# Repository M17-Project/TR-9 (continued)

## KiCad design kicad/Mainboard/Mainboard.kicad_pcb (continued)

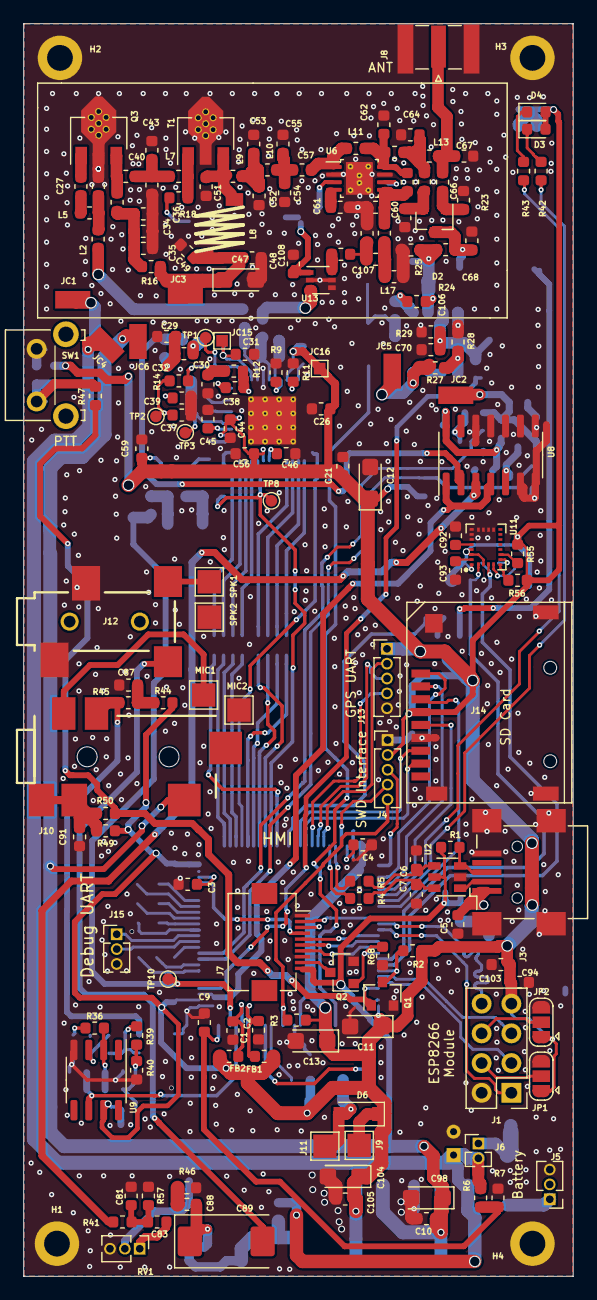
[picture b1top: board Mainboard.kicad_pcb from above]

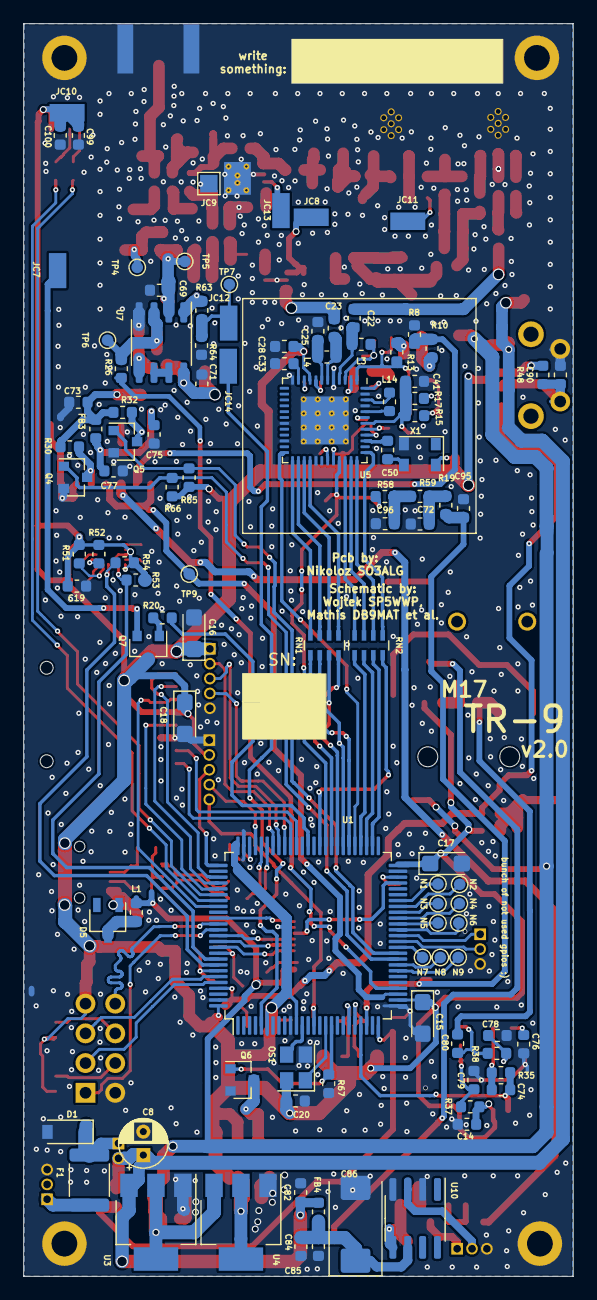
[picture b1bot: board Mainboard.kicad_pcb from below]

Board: 2 copper layers, 47.0 x 107.1 mm, 279 parts (105 on the bottom side), 177 nets.

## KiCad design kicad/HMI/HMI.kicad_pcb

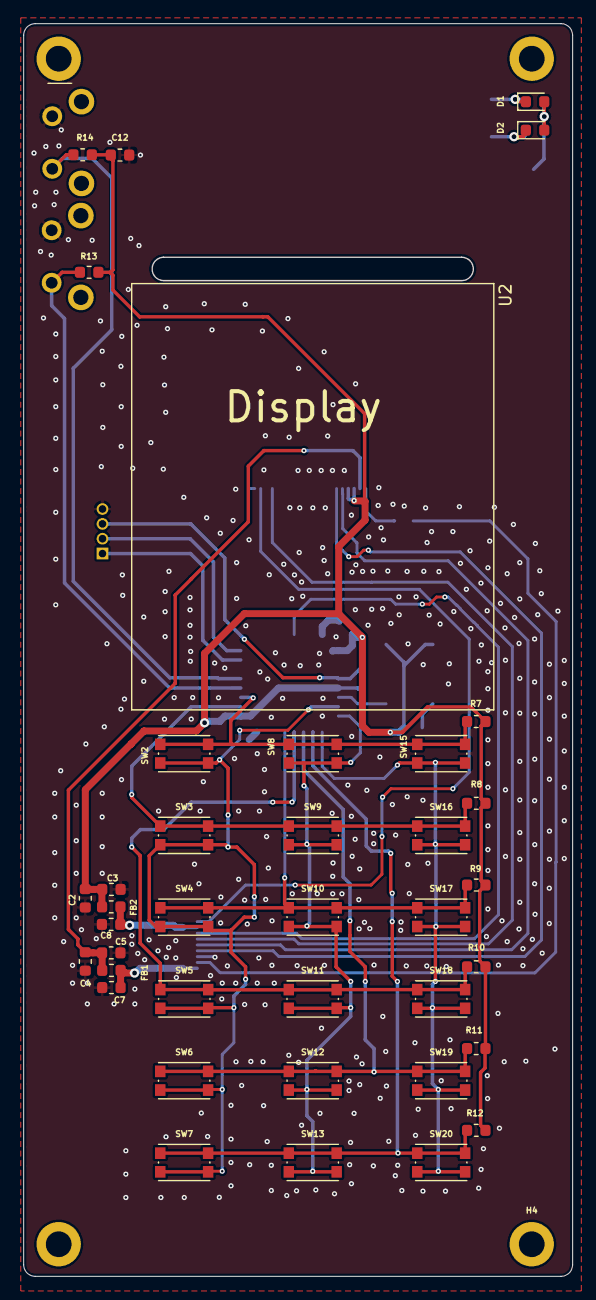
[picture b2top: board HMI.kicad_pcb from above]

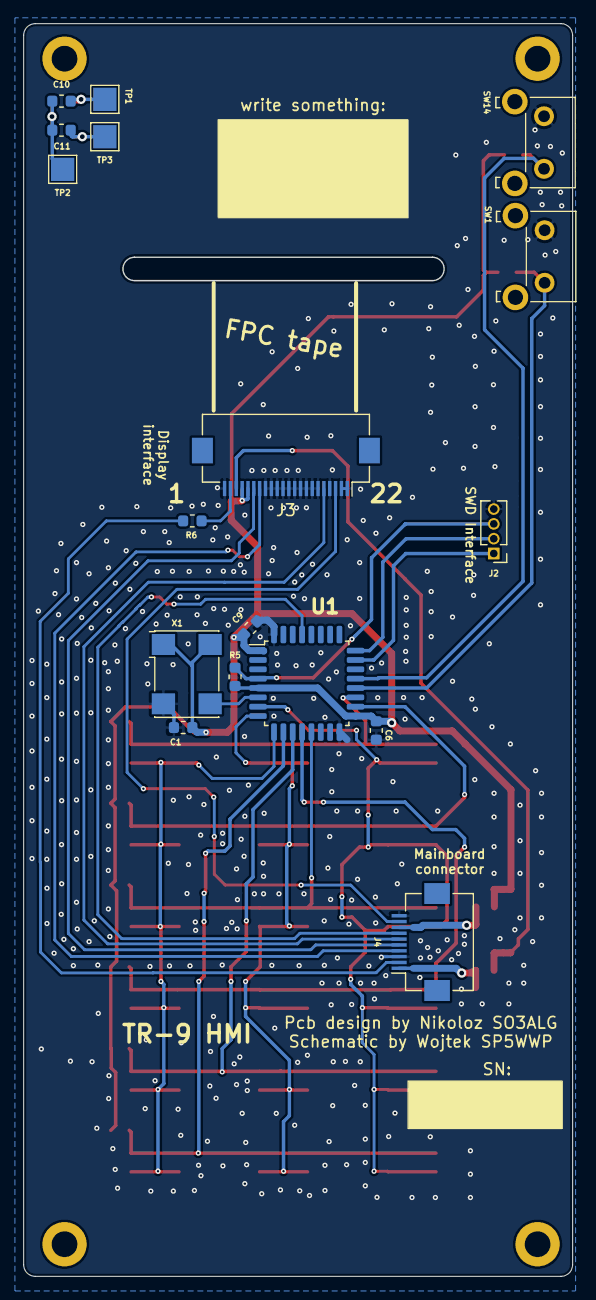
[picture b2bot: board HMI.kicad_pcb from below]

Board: 2 copper layers, 47.0 x 107.2 mm, 59 parts (17 on the bottom side), 30 nets.

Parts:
C1: 10n; C_0603_1608Metric
C2, C4, C7, C8, C10, C11: 100n; C_0603_1608Metric
C3, C5, C6, C9, C12: 1u; C_0603_1608Metric
D1, D2: LED; D_0603_1608Metric
FB1, FB2: Ferrite_Bead; L_0603_1608Metric
H1, H2, H3, H4: M2; MountingHole_2.2mm_M2_ISO14580_Pad
J2: SWD; PinHeader_1x04_P1.27mm_Vertical
J3: FH12-22S-0.5SH; Hirose_FH12-22S-0.5SH_1x22-1MP_P0.50mm_Horizontal
J4: RIBBON; Hirose_FH12-10S-0.5SH_1x10-1MP_P0.50mm_Horizontal
R5: 10k; R_0603_1608Metric
R6: 47R; R_0603_1608Metric
R7, R8, R9, R10, R11, R12, R13, R14: 47k; R_0603_1608Metric
SW1, SW14: SW_Push; SW_Tactile_SKHH_Angled
SW2, SW3, SW4, SW5, SW6, SW7, SW8, SW9, SW10, SW11, SW12, SW13, SW15, SW16, SW17, SW18, SW19, SW20: SW_Push; SW_Push_1P1T_NO_CK_KMR2
TP1, TP2, TP3: TestPoint; TestPoint_Pad_2.0x2.0mm
U1: STM32L011K4Tx; LQFP-32_7x7mm_P0.8mm
U2: DEM 128128A TMH-PW-N; DEM_128128A_TMH-PW-N
X1: ASV-4.000MHZ-EJ-T; Oscillator_SMD_Abracon_ASV-4Pin_7.0x5.1mm

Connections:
+3V3: C1.1, C2.1, C3.1, C6.1, C9.1, C12.1, FB2.2, J3.18, J3.19, R5.1, R7.1, R8.1, R9.1, R10.1, R11.1, R12.1, R13.1, R14.1, U1.1, U1.5, U1.17, X1.1, X1.4
+5V: C4.1, C5.1, FB1.2, J3.20
C1: SW2.2, SW3.2, SW4.2, SW5.2, SW6.2, SW7.2, U1.7
C2: SW8.2, SW9.2, SW10.2, SW11.2, SW12.2, SW13.2, U1.8
C3: SW15.2, SW16.2, SW17.2, SW18.2, SW19.2, SW20.2, U1.9
F1: R13.2, SW1.2, U1.20
F2: R14.2, SW14.2, U1.21
GND: C1.2, C2.2, C3.2, C4.2, C5.2, C6.2, C7.2, C8.2, C9.2, C12.2, J2.4, J3.1, J3.2, J3.4, J3.6, J3.7, J3.8, J3.9, J3.10, J3.11, J3.12, J3.13, J3.14, J3.15, J3.22, J4.3, J4.10, SW1.1, SW14.1, U1.16, U1.32, X1.2
NRST: J2.3, R5.2, U1.4
unnamed: C7.1, FB1.1, J4.1
unnamed: C8.1, FB2.1, J4.8
unnamed: C10.1, C11.1, D1.2, D2.2, TP2.1
unnamed: C10.2, D1.1, TP1.1
unnamed: C11.2, D2.1, TP3.1
unnamed: J3.21, R6.2
OSC: U1.6, X1.3
R1: R12.2, SW7.1, SW13.1, SW20.1, U1.10
R2: R11.2, SW6.1, SW12.1, SW19.1, U1.11
R3: R10.2, SW5.1, SW11.1, SW18.1, U1.12
R4: R9.2, SW4.1, SW10.1, SW17.1, U1.13
R5: R8.2, SW3.1, SW9.1, SW16.1, U1.18
R6: R7.2, SW2.1, SW8.1, SW15.1, U1.19
SPI1_CS: J3.16, J4.4
SPI1_MOSI: J3.5, J4.6
SPI1_SCK: J3.17, J4.5
SWCLK: J2.2, U1.24
SWDIO: J2.1, U1.23
TFT_LED: J4.2, R6.1
TFT_RST: J3.3, J4.9
TX: J4.7, U1.29

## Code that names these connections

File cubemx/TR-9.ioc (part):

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Mcu.Name=STM32F777VITx
Mcu.Package=LQFP100
Mcu.UserName=STM32F777VITx
PA0/WKUP.Signal=ADCx_IN0
PA1.Signal=ADCx_IN1
PA10.Mode=Asynchronous
PA10.Signal=USART1_RX
PA11.Mode=Device_Only
PA11.Signal=USB_OTG_FS_DM
PA12.Mode=Device_Only
PA12.Signal=USB_OTG_FS_DP
PA13.Mode=Serial_Wire
PA13.Signal=SYS_JTMS-SWDIO
PA14.Mode=Serial_Wire
PA14.Signal=SYS_JTCK-SWCLK
PA3.Signal=ADCx_IN3
PA4.Signal=COMP_DAC1_group
PA5.Signal=COMP_DAC2_group
PA8.GPIOParameters=GPIO_Label
PA8.GPIO_Label=GPS_EN
PA8.Signal=GPIO_Output
PA9.Mode=Asynchronous
PA9.Signal=USART1_TX
PB0.GPIOParameters=PinState,GPIO_Label
PB0.GPIO_Label=SPK_AMP_SEL
PB0.PinState=GPIO_PIN_SET
PB0.Signal=GPIO_Output
PB1.GPIOParameters=PinState,GPIO_Label
PB1.GPIO_Label=FM_MOD_SEL
PB1.PinState=GPIO_PIN_SET
PB1.Signal=GPIO_Output
PB10.Mode=Asynchronous
PB10.Signal=USART3_TX
PB11.Mode=Asynchronous
PB11.Signal=USART3_RX
PB13.Mode=Full_Duplex_Master
PB13.Signal=SPI2_SCK
PB14.GPIOParameters=GPIO_PuPd
PB14.GPIO_PuPd=GPIO_PULLUP
PB14.Mode=Full_Duplex_Master
PB14.Signal=SPI2_MISO
PB15.GPIOParameters=GPIO_PuPd
PB15.GPIO_PuPd=GPIO_PULLUP
PB15.Mode=Full_Duplex_Master
PB15.Signal=SPI2_MOSI
PB2.GPIOParameters=GPIO_Label
PB2.GPIO_Label=N7
PB2.Signal=GPIO_Output
PB3.Mode=Simplex_Bidirectional_Master
PB3.Signal=SPI1_SCK
PB4.GPIOParameters=GPIO_Speed,PinState,GPIO_Label
PB4.GPIO_Label=SPI1_CS
PB4.GPIO_Speed=GPIO_SPEED_FREQ_VERY_HIGH
PB4.PinState=GPIO_PIN_SET
PB4.Signal=GPIO_Output
PB5.GPIOParameters=GPIO_Label
PB5.GPIO_Label=BLIGHT_CTRL
PB5.Signal=S_TIM3_CH2
PB6.Mode=I2C
PB6.Signal=I2C1_SCL
PB7.Mode=I2C
PB7.Signal=I2C1_SDA
PB8.GPIOParameters=PinState,GPIO_Label
PB8.GPIO_Label=WIFI_RST
PB8.PinState=GPIO_PIN_SET
PB8.Signal=GPIO_Output
PB9.GPIOParameters=GPIO_Label
PB9.GPIO_Label=WIFI_EN
PB9.Signal=GPIO_Output
PC1.GPIOParameters=PinState,GPIO_Label
PC1.GPIO_Label=XO_EN
PC1.PinState=GPIO_PIN_SET
PC1.Signal=GPIO_Output
PC12.GPIOParameters=GPIO_PuPd
PC12.GPIO_PuPd=GPIO_PULLDOWN
PC12.Mode=SD_1_bit
PC12.Signal=SDMMC1_CK
PC2.GPIOParameters=GPIO_Label
PC2.GPIO_Label=VIBRATE
PC2.Signal=GPIO_Output
PC4.GPIOParameters=GPIO_Label
PC4.GPIO_Label=N9
PC4.Signal=GPIO_Output
PC5.GPIOParameters=GPIO_Label
PC5.GPIO_Label=N8
PC5.Signal=GPIO_Output
PC6.GPIOParameters=GPIO_Speed,PinState,GPIO_Label
PC6.GPIO_Label=LNA_EN
PC6.GPIO_Speed=GPIO_SPEED_FREQ_HIGH
PC6.PinState=GPIO_PIN_SET
PC6.Signal=GPIO_Output
PC8.GPIOParameters=GPIO_PuPd
PC8.GPIO_PuPd=GPIO_PULLUP
PC8.Mode=SD_1_bit
PC8.Signal=SDMMC1_D0
PD0.GPIOParameters=PinState,GPIO_Label
PD0.GPIO_Label=LED_GRN
PD0.PinState=GPIO_PIN_SET
PD0.Signal=GPIO_Output
PD1.GPIOParameters=PinState,GPIO_Label
PD1.GPIO_Label=LED_RED
PD1.PinState=GPIO_PIN_SET
PD1.Signal=GPIO_Output
PD10.GPIOParameters=GPIO_Speed,GPIO_Label
PD10.GPIO_Label=ADF_SDATA
PD10.GPIO_Speed=GPIO_SPEED_FREQ_VERY_HIGH
PD10.Signal=GPIO_Output
PD11.GPIOParameters=GPIO_Label
PD11.GPIO_Label=ADF_SREAD
PD11.Signal=GPIO_Input
PD12.GPIOParameters=GPIO_Speed,GPIO_Label
PD12.GPIO_Label=ADF_SCLK
PD12.GPIO_Speed=GPIO_SPEED_FREQ_VERY_HIGH
PD12.Signal=GPIO_Output
PD13.GPIOParameters=GPIO_Label
PD13.GPIO_Label=ADF_SWD
PD13.Signal=GPXTI13
PD14.GPIOParameters=GPIO_Label
PD14.GPIO_Label=ADF_MUX_OUT
PD14.Signal=GPXTI14
PD2.GPIOParameters=GPIO_PuPd
PD2.GPIO_PuPd=GPIO_PULLUP
PD2.Mode=SD_1_bit
PD2.Signal=SDMMC1_CMD
PD4.GPIOParameters=GPIO_Label
PD4.GPIO_Label=TFT_RST
PD4.Signal=GPIO_Output
PD5.Mode=Asynchronous
PD5.Signal=USART2_TX
PD6.Mode=Asynchronous
PD6.Signal=USART2_RX
PD7.Mode=Simplex_Bidirectional_Master
PD7.Signal=SPI1_MOSI
PD8.GPIOParameters=GPIO_Speed,PinState,GPIO_Label
PD8.GPIO_Label=ADF_CE
PD8.GPIO_Speed=GPIO_SPEED_FREQ_VERY_HIGH
PD8.PinState=GPIO_PIN_SET
PD8.Signal=GPIO_Output
PD9.GPIOParameters=GPIO_Speed,GPIO_Label
PD9.GPIO_Label=ADF_SLE
PD9.GPIO_Speed=GPIO_SPEED_FREQ_VERY_HIGH
PD9.Signal=GPIO_Output
PE0.GPIOParameters=GPIO_PuPd,GPIO_Label,GPIO_ModeDefaultEXTI
PE0.GPIO_Label=PTT_INT
PE0.GPIO_ModeDefaultEXTI=GPIO_MODE_IT_RISING_FALLING
PE0.GPIO_PuPd=GPIO_PULLUP
PE0.Signal=GPXTI0
PE10.GPIOParameters=GPIO_Label
PE10.GPIO_Label=N5
PE10.Signal=GPIO_Output
PE11.GPIOParameters=GPIO_Label
PE11.GPIO_Label=N4
PE11.Signal=GPIO_Output
PE12.GPIOParameters=GPIO_Label
PE12.GPIO_Label=N3
PE12.Signal=GPIO_Output
PE13.GPIOParameters=GPIO_Label
PE13.GPIO_Label=N2
PE13.Signal=GPIO_Output
PE14.GPIOParameters=GPIO_Label
PE14.GPIO_Label=N1
PE14.Signal=GPIO_Output
PE6.GPIOParameters=GPIO_Label
PE6.GPIO_Label=TRX_SW
PE6.Signal=GPIO_Output
PE7.Mode=Asynchronous
PE7.Signal=UART7_RX
PE8.Mode=Asynchronous
PE8.Signal=UART7_TX
PE9.GPIOParameters=GPIO_Label
PE9.GPIO_Label=N6
PE9.Signal=GPIO_Output
PH0/OSC_IN.Mode=HSE-External-Clock-Source
PH0/OSC_IN.Signal=RCC_OSC_IN
PH1/OSC_OUT.Mode=HSE-External-Clock-Source
PH1/OSC_OUT.Signal=RCC_OSC_OUT
RCC.HSE_VALUE=16000000
RCC.SYSCLKFreq_VALUE=216000000
RCC.SYSCLKSource=RCC_SYSCLKSOURCE_PLLCLK
board=custom

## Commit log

2019-01-18 sch+pcb
2019-01-18 cubemx+sw4stm32
2019-01-27 Add files via upload
    I have probably finally fixed interrupt priorities :) also - PTT action is now interrupt driven
2019-03-17 Add files via upload
    +ADXL345
2019-05-28 Add files via upload
    WDS3 config file
2019-12-11 Update README.md
    Added PoC info.
2019-12-26 Initial WIP KiCAD schematics
    Initial commit of the schematics redrawn in KiCAD with some fixes applied. Still needs to be cleaned up
2019-12-26 Removed Eagle files
    Transitioning from Eagle to KiCAD
2019-12-27 Added power detector
    Added two missing inductors in the RF output switch and started work on the power detection circuit
2019-12-30 Updated WIP schematics
2020-01-14 Add files via upload
    * replaced Q7 with BSS138
    * new HMI connector (for keypad and display)
2020-01-18 Added ADF7021
2020-01-18 Added BGA6589 gain stage
2020-01-22 Add files via upload
    replaced TCXO with ECS-TXO-3225-122.8-TR
2020-01-22 Add files via upload
    added 2 buttons: F1 and F2
2020-01-27 Add files via upload
    added a resistor to form a voltage divider network (at pin 3 of LM2904) and changed the cap from 100n to 10n
2020-01-28 Annotated parts
2020-01-28 Revert "Annotated parts"
    This reverts commit b309e3bfe0d7a41f96c10818008ed221b92f9604.
2020-01-28 Annotated parts, again.
2020-01-31 Started assigning footprints
2020-02-01 Add files via upload
    ADF7021 pin 36: SPI1_SCK -> SPI2_SCK
2020-02-01 Add files via upload
    C94 -> 10uF
2020-02-04 Add files via upload
    added a Sallen-Key 6kHz anti-aliasing lowpass filter between the ADF (SWD pin) and STM32 (ADC input)
2020-02-08 Add files via upload
    assigned some more footprints
2020-02-09 Add files via upload
    fixed U7 name (LM2904A)
2020-02-13 - Added footprint library - TR-9 - Imported a few footprints - Designed a MicroSD card slot footprint - Assignment footprints to corresponding elements on schematic
2020-02-13 added more footprints
2020-02-13 Assigned SMA as antenna connector
2020-02-13 - designed and added footprint for L8 RF inductor
2020-02-13 Added HMC RF switch Corrected SOIC footprints assignment
2020-02-14 Added thermal vias to BGA6589 footprint Corrected USART to UART
2020-02-14 Added thermal pads to AFT05MS004NT1 RF transistor footprint
2020-02-14 started working on PCB - power supply completed plotted new PDF schematic
2020-02-14 added a capacitor for GPS voltage line footprints - expanded RF transistors ground plane generated new PDF added authors
2020-02-15 Add files via upload
    i've set some footprints and changed that 10-pin connector pin order
2020-02-15 adf7021 and companion passives are quite sorted now
2020-02-15 PCB - connected microSD card to STM32 & USB frontend path routed added a schottky diode PMEG4005ET.215 footprint changed connector J7 pinout - TFT_RST swapped with UART2_RX! schootky diode added to i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
2020-02-15 Corrected outline in PCB
2020-02-15 another pin swap
2020-02-16 PCB updated - added MIC_AMP & SPK_AMP
2020-02-16 added pcb author
2020-02-16 Working on PCB
2020-02-16 PCB update
2020-02-16 Module with OPA340UA U9 made smaller - more space for other modules
2020-02-16 Power supply part occupies less space on pcb!
2020-02-17 added ESP8266EX
2020-02-17 4066 based switch module connected
2020-02-17 PCB improvement, new PDF plot
2020-02-17 optimised an RF section elements placement
2020-02-18 rf part almost done
2020-02-18 PCB improvement - added module with U13
2020-02-18 Critical J7 header pinout change! New schematic PCB plot
2020-02-18 added 5V line to the HMI ribbon
2020-02-19 added voltage divider at the PA_BIAS
2020-02-19 forgotten PDF :)
2020-02-19 added 5V LM2904 supply
2020-02-19 smaller RF Power part + diode pins swap + PLOT PDF
2020-02-19 further improvement of RF Power Amplifier section
2020-02-20 Peak to peak voltage meter added
2020-02-20 added vibration motor
2020-02-20 pinout update
2020-02-20 RF path improvement, changing speaker and microphone headers to soldering pads, plotting new PDF
2020-02-20 pin correct
2020-02-21 added some decoupling caps, pull ups/downs
2020-02-22 RF power amp, and RF chipset on pcb
2020-02-22 pdf plot
2020-02-22 RF chipset elements optimalisation
2020-02-22 board longer - 1cm more
2020-02-22 new outline
2020-02-22 kenwood adapter on pcb ,new PDF plot
2020-02-22 more changes
2020-02-23 cosmetic changes
2020-02-23 Power lines spread around the pcb, kenwood connector(2 jacks), J4 and J13 placed in better place
2020-02-23 shield added
2020-02-24 Shielding outline correction, and etc...
2020-02-25 started to reorganize an elements - further optimisation
2020-02-25 further components optimisation
2020-02-25 further changes - RF part
2020-02-26 UART3 swapped with UART2 - now keyboard uses UART3, and WIFI uses UART2; added ladder for ADF7021 data lines; further pcb improvement(shielding for ADF7021 part)
2020-02-26 correction on schematic - UART3 with UART2 swap; new PDF plot further pcb improvement
2020-02-27 further pcb improvement
2020-02-27 further improvement of pcb
2020-02-28 pcb improvement
2020-02-28 more pcb improvements
2020-02-29 Added 2,4GHz antenna; added RF matching Pi circuit; plotted new PDF
2020-02-29 led-s connected
2020-03-01 Drawn meanders for flash memory of ESP32 chip. trace difference max +- 0,2mm Added status diodes
2020-03-01 improvement
2020-03-01 a small changes
2020-03-02 cleanup, annotation
2020-03-02 corrected FPC footprint assignment
2020-03-03 added SWD pins to the micro, started laying out the board
2020-03-03 added C106 (10pF)
2020-03-04 added 6 testpoints
2020-03-06 HMI - changed SW1 and SW14 button footprint; Mainboard - further changes; TR-9 library, correcting footprint
2020-03-23 changed Sallen-Key filter RC values (to 6.8k and 2.2n)
2020-03-24 updated sigma-delta filter topology
2020-04-21 Add files via upload
    added BGA2874 test board gerber files
2020-05-02 added BGA2874 RX amplifier & highpass LC filter(schematic & pcb) pcb design nearly done ~95%
2020-05-02 more changes on pcb
2020-05-04 ADF7021 config file
2020-05-16 added RF switch on-off transistor, plotted new schematic
2020-05-18 fixed p-mos alignment :)
2020-05-31 Added some vias and forgotten power supply lines & plotted pdf schematic
2020-06-10 added vias, and long soldering pads(for shielding) around RF Amplifier part, added more vias near STM32, added 3D visualizaton of PCB!
2020-06-11 added 9 TestPoints called N1 ... to N9, which allow to debug STM32, and experiment with more peripherals in the future. Plotted PDF schematic
2020-06-27 Move cubemx → cubemx_old
2020-06-27 added a JCx symbols - these are Jumper Cables - them are used to avoid EMI diseaster when trying to route Power signals under RF 50 ohm trace - also added them to PCB + Schematic in PDF plotted; TODO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
2020-07-05 few fixes
2020-07-05 more jumper added
2020-07-08 removed ESP8266 and it's circuitry; instead added a Pin Headers 2x4 for soldering in ESP8266 SoM; changed vias to manufacturable by JlcPcb; plotted PDF
2020-07-08 changed BATT cap
2020-07-11 some small changes
2020-07-11 more changes on RF chipset - adding jumperpoint 15&16
2020-07-12 added new PCB photos
2020-07-13 added jumpers on GPIO0 and GPIO2 for ESP8266 module; described pin headers on PCB; connected pin 16 of STM32 to Power Down pin in OS1; plotted schematic in PDF
2020-07-14 added more vias
2020-07-14 informations about connectors on PCB; more vias for better signal integrity; new pcb 3D photos
2020-07-14 credit labels moved; added blank place for label
2020-07-14 added new PNGs with pcb
2020-07-15 added Jumper cable connections description -> moved "M17" and "TR-9" labels -> added label "v 2.0" -> plotted PDF
2020-07-15 changed OscillatorON to XO_EN -> added "SN:" title on PCB -> plotted new PDF
2020-07-15 optimized vias sizes
2020-07-22 HMI: added design of PCB -> plotted PDF -> plotted production output - Gerbers -> HMI is READY!!
2020-07-22 Mainboard: plotted PDF -> added design of PCB -> plotted Gerbers -> Mainboard ready!
2020-07-26 Added missing 3D models
2020-07-26 new 3d models
2020-07-29 added few values in BOM
2020-07-29 Mainboard: List of components -> Added TempCoef types, voltage values and tolerance for capaciors; added power values and tolerance for resistors
2020-07-29 Mainboard: added new PCB 3D visualisation
2020-07-29 HMI: Added 3D visualisation of PCB
2020-07-30 added new InteractiveBOM
2020-07-30 HMI -> corrected PCB to mainboard form factor, added diodes
2020-07-31 Generated Gerbers for new HMI, corrected BOM for Mainboard
2020-07-31 aded new visualisation of 3D of HMI
2020-07-31 HMI: widened space between keys on keypad -> generated new Gerbers & STEP
2020-08-01 HMI: some changes - not ready board YET!
2020-08-01 HMI: Added space over display + Mainboard connector placement correction -> Generated GERBER + STEP + 3D visualisation
2020-08-02 HMI: added labels on silksScreen -> added one capacitor -> generated new PDF -> generated new GERBERS -> NEW STEP!
2020-08-08 test firmware
2020-08-08 display update
2020-08-28 case design files for 3D printing
2020-09-13 Mainboard: corrected C47 & properly described C76, C79, C87 & assigned value to R20 & L1 is now Fair-Rite 2506032217Y2 & Volume pot is now Alps RK0971111Z32
2020-09-13 added "//DONE" marker to errata
2020-09-23 Add files via upload
    added: Codec2, hardware CRC calculation unit
    fixed: FN starts at zero
    more improvements on MoIP
2020-09-23 add in radio capabilities
    add in radio capabilities
2020-09-28 Update CODEPLUG
2020-10-03 fixed buffering issue
2020-10-12 Revert "Add files via upload"
    This reverts commit 58dcf9b5dfb61d827b61158b1a3efca5b5b818b6.
2020-10-29 Address R20 value
2020-11-11 Adding .gitignore, cleaning up kicad cruft
2020-11-14 cleanup redundant and old folders, new cubemx place is m17-project/TR-9_firmware repo
2020-11-14 update README with links
2020-11-14 rm codeplug/, which is now at corresponding m17-project repo
2020-11-15 Removing "plt" files, generated output
2020-11-15 Library STEP files should be under .3dshapes
2020-11-15 Marking as SMD, correcting path to model
2020-11-15 Correcting 3D model paths, keepout
2020-11-15 Updating PCB with links to corrected 3D models
2020-11-15 Updating references to 3dshapes
2020-11-15 Updating origin for PCBs
2020-11-15 Upading documentation for SD card holder
2020-11-19 Adding footprint for DEM Display
    Footprint exterior dimensions, glass and display area are to scale.
    Other items, such as the tabs for securing the glass, and thickness
    of the PCB/glass are decorative.
2020-11-19 Adding mounting holes, U2. Corrected part number for J3.
2020-11-19 Better aligning key components to grid, closes #18
    Also:
    - Added 3D step model for display
    - Corrected DRC issues
    - Added 2mm chamfer on PCB edges
    - Reduced size for FPC slot, added rounded corners
    - Moved C12 to avoid being too close to display
2020-11-19 Fixing 3D models for push buttons
2020-11-19 Add thermals on ground plane, extend ground plane to PCB edges
2020-11-19 Relocating J2 from underneath display
    This is a temporary fix. With issue #7, this part will change.
2020-11-19 Oops, correcting display 3d model offset
2020-11-20 Add files via upload
    PDF restored
2022-01-27 Update to KiCad v6
2022-01-27 Add C106 in parallel to R21
2022-02-05 Delete backups
    * Delete kicad/HMI/HMI-backups directory
    * Delete kicad/Mainboard/Mainboard-backups directory
